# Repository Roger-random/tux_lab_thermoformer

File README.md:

# Tux-Lab Thermoforming Machine project

Files related to getting the Tux-Lab thermoforming machine back up and running.

## controls/AcrylicRelayPanel

Files for laser-cutting the relay panel and the toggle switches panel

## pi_touch_ui

The initial goal is to get the machine up and running with manual toggle switches. But being the tinkerer type - we know we will want to do more. This respository starts with an effort to create a machine control UI with PyQt5. The idea is to mount a Raspberry Pi the machine and control the machine this way.

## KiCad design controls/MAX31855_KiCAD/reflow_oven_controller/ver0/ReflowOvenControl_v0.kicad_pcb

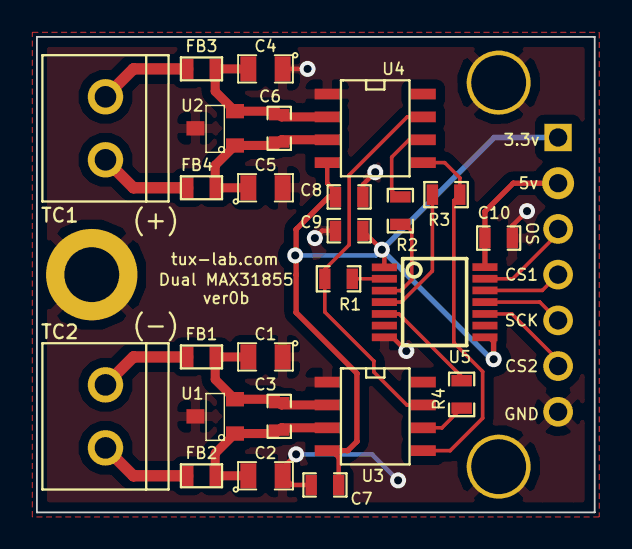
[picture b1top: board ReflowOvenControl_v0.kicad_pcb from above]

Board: 2 copper layers, 31.0 x 26.4 mm, 29 parts (0 on the bottom side), 23 nets.

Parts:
C1, C2, C4, C5: C; SM0805
C3, C6, C7, C8, C9, C10: C; SM0603_Capa
FB1, FB2, FB3, FB4: FILTER; SM0603
MountingHole-4-40, MountingHole-4-40#2, MountingHole-4-40#3: VAL**; MountingHole-4-40
P1: TC2; TermB_OnShore_3d5mm
P2: TC1; TermB_OnShore_3d5mm
P3: CONN_7; SIL-7
R1, R2, R3, R4: R; SM0603_Resistor
U1, U2: NUP2105; SOT23
U3, U4: MAX31855; SO8E
U5: TXB0104; SSOP14

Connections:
3.3V: C7.1, C8.1, C9.2, P3.1, U3.4, U4.4, U5.1, U5.8
5V: C10.2, P3.2, U5.14
CS1: P3.4, U5.12
CS2: P3.6, U5.10
GND: C1.1, C2.2, C4.1, C5.2, C7.2, C8.2, C9.1, C10.1, P3.7, U1.3, U2.3, U3.1, U4.1, U5.7
unnamed: C1.2, C3.1, FB1.2, U1.2, U3.2
unnamed: C2.1, C3.2, FB2.2, U1.1, U3.3
unnamed: C4.2, C6.1, FB3.2, U2.2, U4.2
unnamed: C5.1, C6.2, FB4.2, U2.1, U4.3
unnamed: FB1.1, P1.1
unnamed: FB2.1, P1.2
unnamed: FB3.1, P2.1
unnamed: FB4.1, P2.2
unnamed: R1.1, U3.7, U4.7
unnamed: R1.2, U5.2
unnamed: R2.1, U4.6
unnamed: R2.2, U5.3
unnamed: R3.1, U3.5, U4.5
unnamed: R3.2, U5.4
unnamed: R4.1, U3.6
unnamed: R4.2, U5.5
SCK: P3.5, U5.11
SO: P3.3, U5.13

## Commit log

2017-10-03 Status bar implementation
2017-10-04 .gitignore for Python
2017-10-04 Foiled by 'QMainWindow takes ownership of the widget pointer and deletes it at the appropriate time'
2017-10-04 takeCentralWidget (new in Qt 5.2) stops mainwindow from deleting
2017-10-05 ExpandToggleButton (initial implementation)
2017-10-05 Moving magic strings to constants + minor code reorg
2017-10-05 Use QGroupBox, create StateLabel
2017-10-05 Navigation Bar initial implementation
2017-10-05 IOManager rough draft
2017-10-05 UIState widget as state template
2017-10-05 MachineState base class + ActiveState
2017-10-05 LoadingState
2017-10-05 HeatingState
2017-10-05 DropState
2017-10-05 FormingState
2017-10-06 CompleteState
2017-10-06 Keep CompleteState magnet button in sync on each run
2017-10-06 PiGPIO initial integration runs on Pi only
2017-10-06 Pin 5 and 6 leaks power on startup, before any code runs. Do not use them for driving relays.
2017-10-07 Increase button label text size
2017-10-07 First test with input level change callback. We'll need to perform debouncing.
2017-10-08 Use threading.Timer for debouncing pin level changes
2017-10-08 Remove debugging print() for debounce routine
2017-10-08 GPIOLabel finally does what its name says: reflect GPIO pin state in its visual style.
2017-10-08 Switch from OnOffLabel to GPIOLabel. Now the status labels are actually status of the pins as read from pigpiod. The IOManager is no longer responsible for manually switching them.
2017-10-09 DelayedCall for time-delayed callback on UI thread
2017-10-09 (1) ActiveState use DelayedCall to wait 2 seconds between turnOn. (2) DirectControlState tracks its buttons and synchronizes their states with the GPIO pin upon onEntry
2017-10-09 (1) Loading state 'back' now goes to Standby. (2) ActiveState renamed to StartupState
2017-10-09 StartupState now tells user what's going on via new CenteredLabel() on-screen
2017-10-20 KiCAD relay board revised layout. Inkscape acrylic relay board.
2017-10-21 added QVac Acrylic mini control panel
2017-10-22 removed QVac_RelayPanel
2017-10-23 Move Raspberry Pi touchscreen project to subdirectory
2017-10-23 Remove Raspberry Pi touchscreen files from root directory of project
2017-10-23 pigpio_stub first draft
2017-10-26 Update README to reflect new directory structure
2017-10-26 Added Schematic
2017-10-27 added kicad files for MAX31855 TC amp board
